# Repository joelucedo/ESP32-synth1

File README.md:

## ESP32 SYNTH
***ESP32 Wrover E/IE based synthesizer***

## STATUS
Work in progress.
</br>
## SPECS
Audio in/out and headphone,  MIDI in/out/thru, 16 pot + 1 volume pot, USB-C, reset switch

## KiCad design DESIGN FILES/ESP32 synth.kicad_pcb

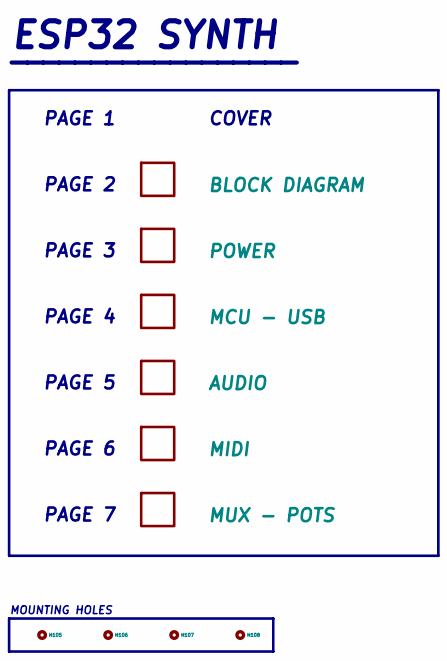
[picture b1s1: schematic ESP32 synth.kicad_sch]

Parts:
H105, H106, H107, H108: MountingHole; MountingHole_2.5mm

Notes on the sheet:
PAGE 4
COVER
PAGE 2
PAGE 5
ESP32 SYNTH
PAGE 6
MOUNTING HOLES
__________________
PAGE 7
PAGE 1
PAGE 3

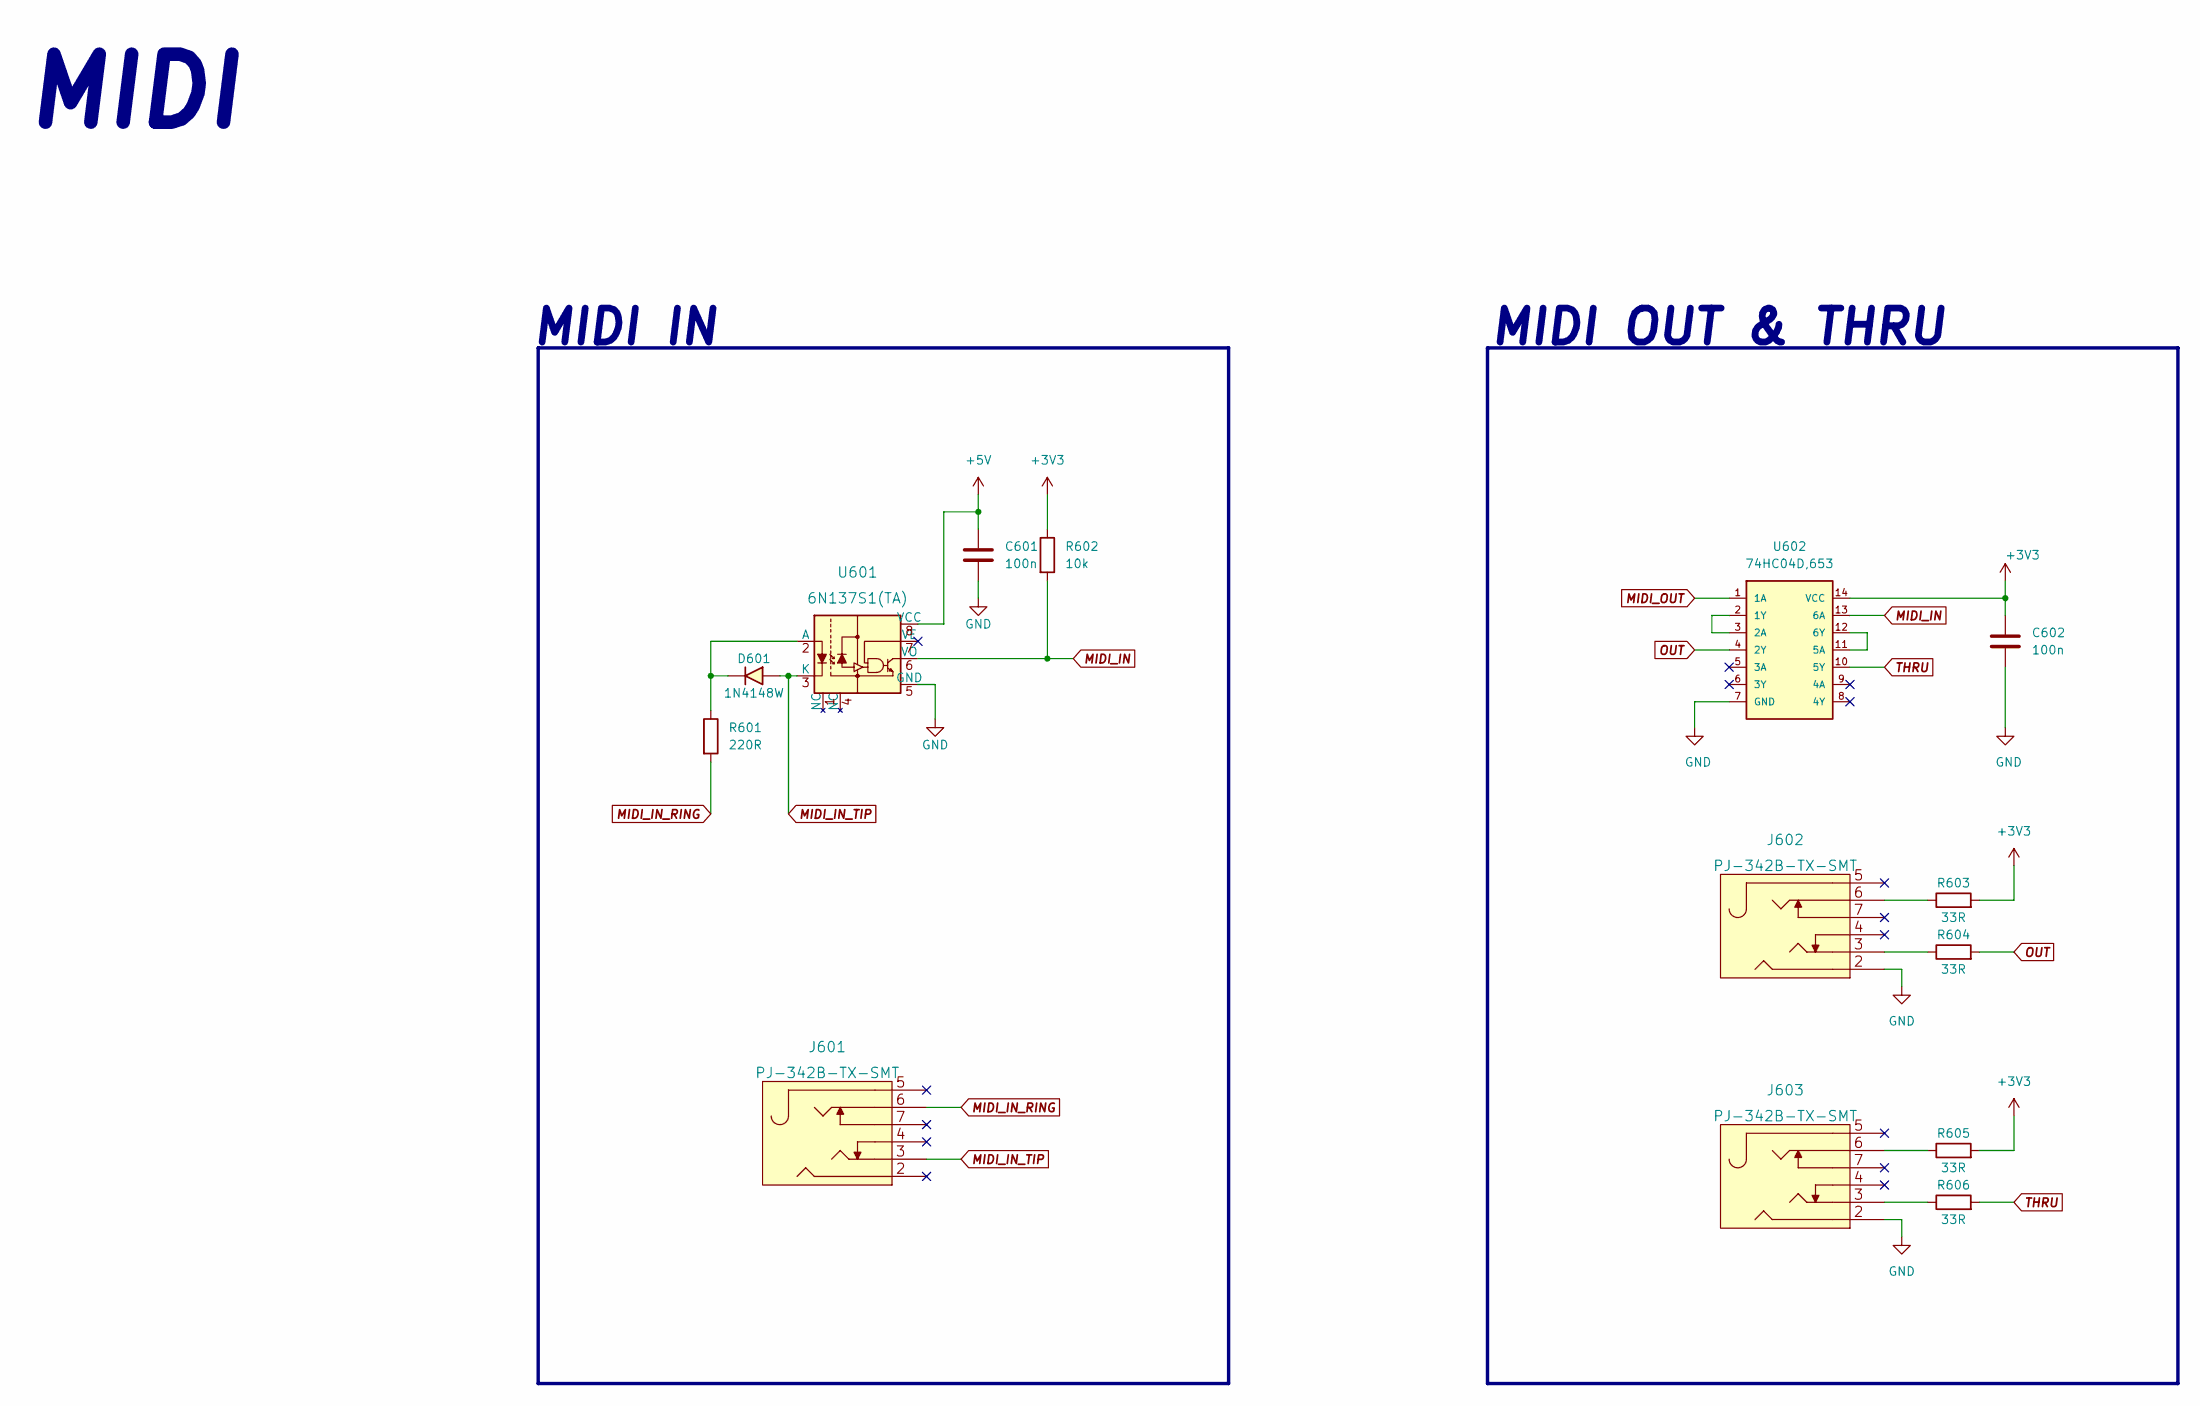
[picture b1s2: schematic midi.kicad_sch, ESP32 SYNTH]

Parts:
C601, C602: 100n; CC0603KRX7R9BB104_0603
D601: 1N4148W; 1N4148W_SOD-123
J601, J602, J603: PJ-342B-TX-SMT
R601: 220R; 0603WAF2200T5E
R602: 10k; 0603WAF1002T5E
R603, R604, R605, R606: 33R; 0603WAF330JT5E
U601: 6N137S1(TA); 6N137S1_TA_SMD-8P; MPN 6N137; Digi-Key_PN 160-1791-ND
U602: 74HC04D,653; 74HC04D_653_SOIC-14; MPN 74HC04D,653

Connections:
+3V3: C602.1, R602.1, R603.2, R605.2, U602.14 (VCC); also elsewhere on the board
+5V: C601.1, U601.8 (VCC); also elsewhere on the board
GND: C601.2, C602.2, J602.2, J603.2, U601.5 (GND), U602.7 (GND); also elsewhere on the board
MIDI_IN: R602.2, U601.6 (VO), U602.13 (6A); also elsewhere on the board
MIDI_IN_RING: J601.6, R601.2
MIDI_IN_TIP: D601.2 (A), J601.3, U601.3 (K)
MIDI_OUT: U602.1 (1A); also elsewhere on the board
unnamed: D601.1 (K), R601.1, U601.2 (A)
unnamed: J602.3, R604.1
unnamed: J602.6, R603.1
unnamed: J603.3, R606.1
unnamed: J603.6, R605.1
unnamed: U602.2 (1Y), U602.3 (2A)
unnamed: U602.11 (5A), U602.12 (6Y)
OUT: R604.2, U602.4 (2Y)
THRU: R606.2, U602.10 (5Y)

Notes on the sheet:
MIDI OUT & THRU
MIDI IN
MIDI

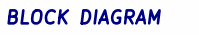
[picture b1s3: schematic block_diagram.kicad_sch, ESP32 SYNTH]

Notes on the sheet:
BLOCK DIAGRAM

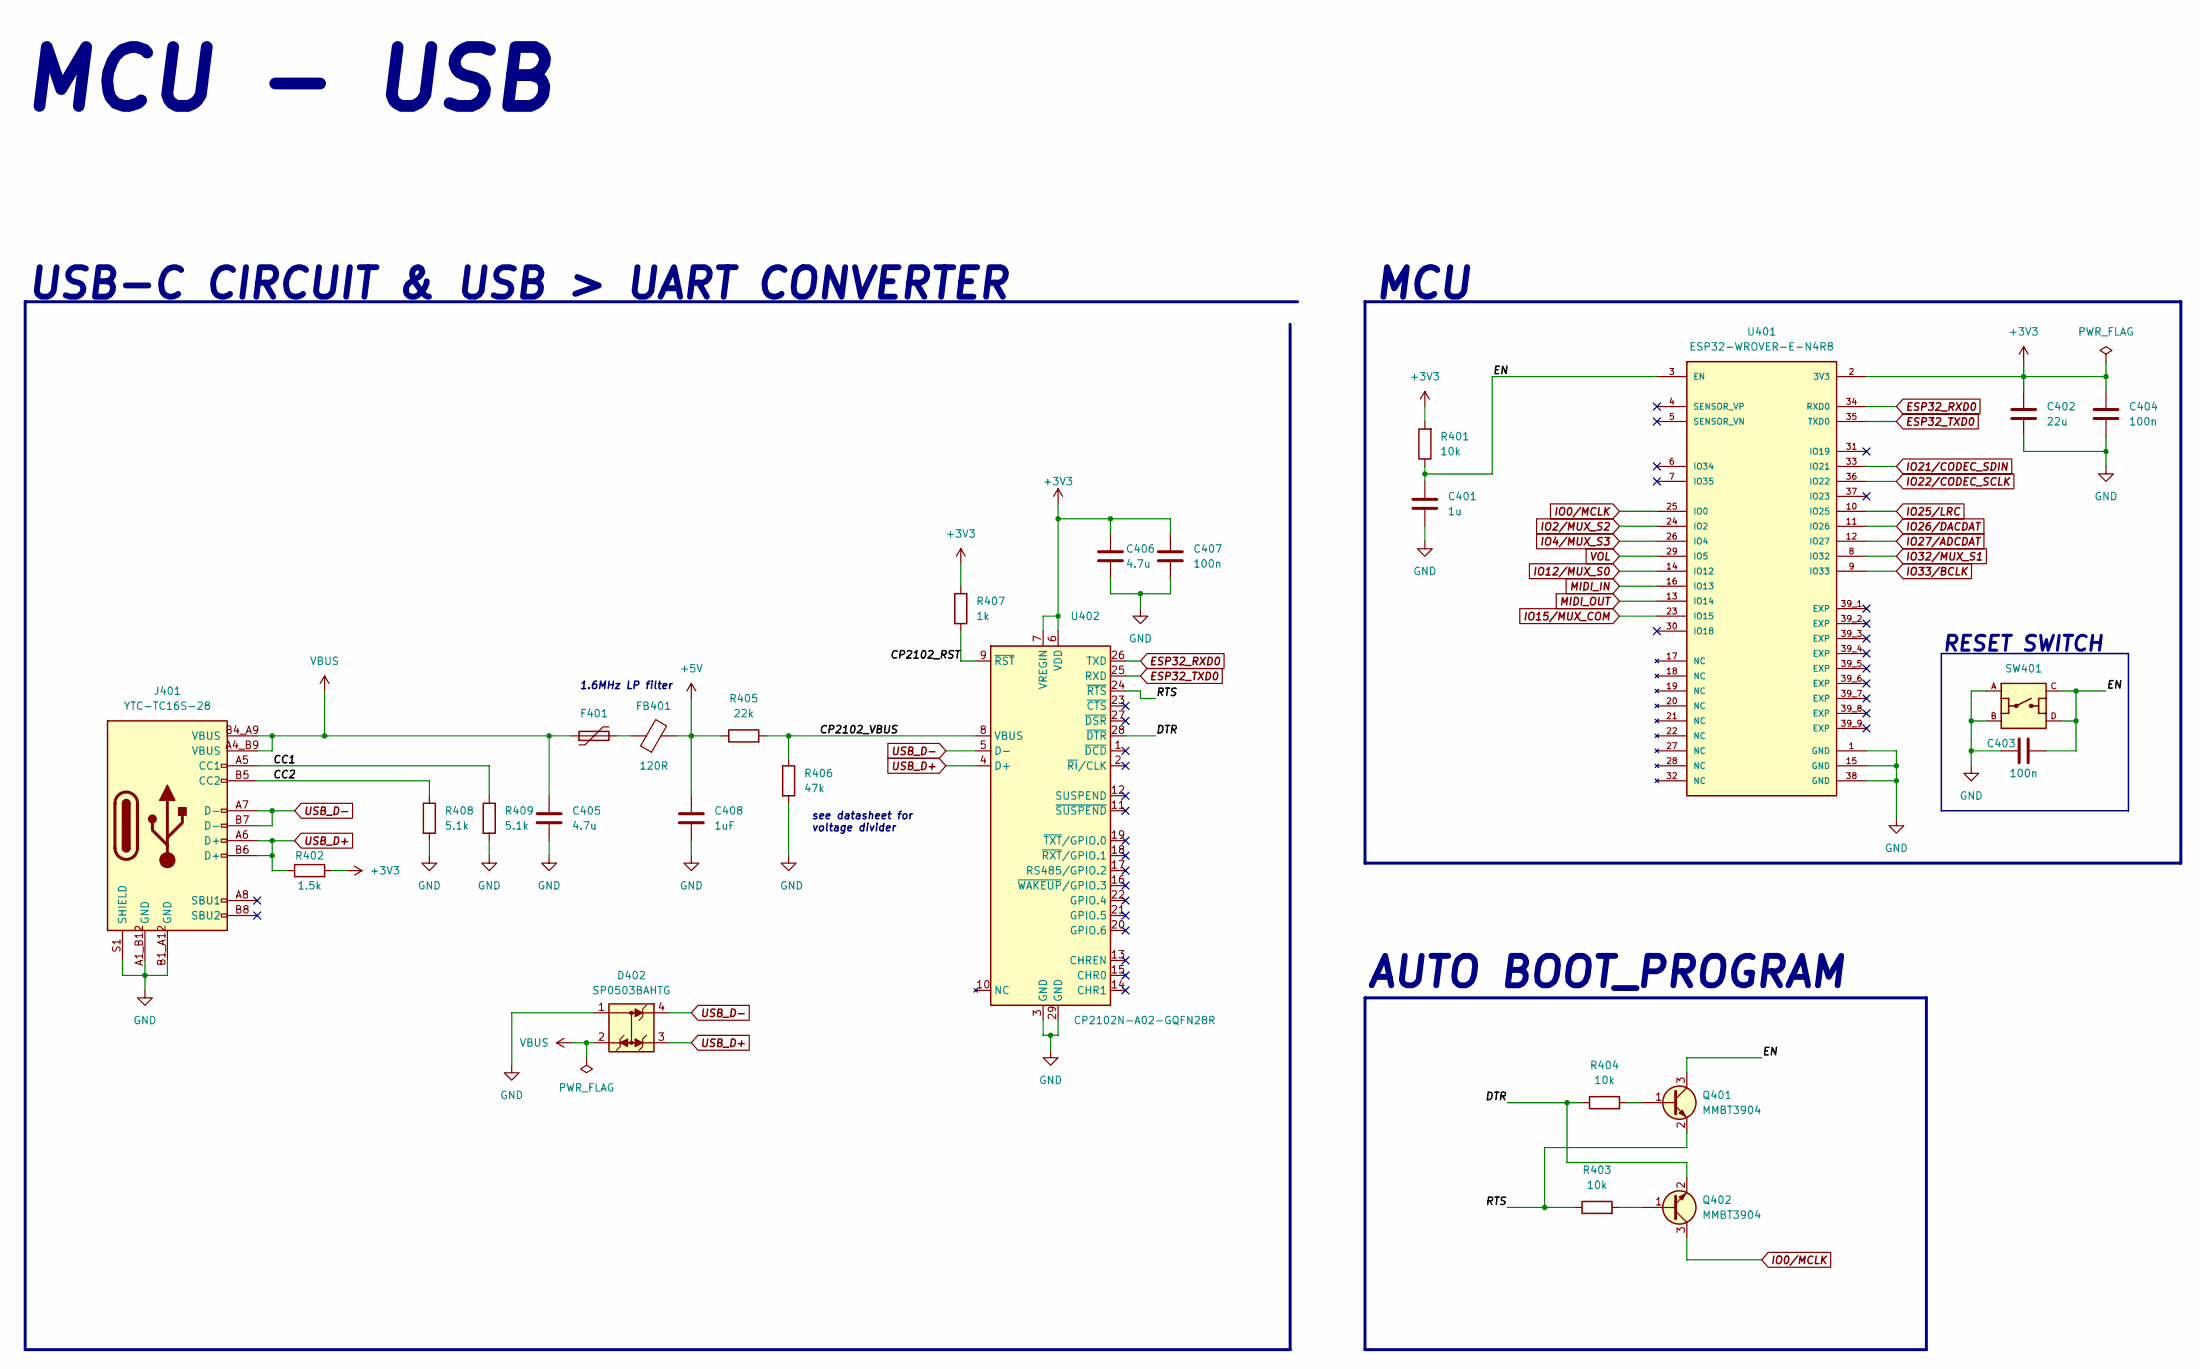
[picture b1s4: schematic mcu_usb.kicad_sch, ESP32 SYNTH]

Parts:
C401: 1u; CL10A105KB8NNNC_0603
C402: 22u; 0603_CL10A226MQ8NRNC
C403, C404, C407: 100n; CC0603KRX7R9BB104_0603
C405, C406: 4.7u; CL10A475KO8NNNC_0603
C408: 1uF; CL10A105KB8NNNC_0603
D402: SP0503BAHTG; SP0503BAHTG_SOT-143; MPN SP0503BAHTG; Digi-Key_PN F2715CT-ND
F401: SMD0805P020TF; 0805_SMD0805P020TF
FB401: 120R; 0603_BLM18AG121SN1D
J401: YTC-TC16S-28
Q401, Q402: MMBT3904; MMBT3904_SOT-23
R401, R403, R404: 10k; 0603WAF1002T5E
R402: 1.5k; CQ03WAJ0152T5E
R405: 22k; 0603WAF2202T5E
R406: 47k; 0603WAF4702T5E
R407: 1k; 0603WAF1001T5E
R408, R409: 5.1k; 0603WAF5101T5E
SW401: TS-1187A-B-A-B; TS-1187A-B-A-B_smd
U401: ESP32-WROVER-E-N4R8; XCVR_ESP32-WROVER-E-N4R8; PARTREV 1.6
U402: CP2102N-A02-GQFN28R; CP2102N-A02-GQFN28R_QFN-28

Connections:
+3V3: C402.1, C404.1, C406.1, C407.1, R401.2, R402.2, R407.1, U401.2 (3V3), U402.6 (VDD), U402.7 (VREGIN); also elsewhere on the board
+5V: C408.1, FB401.2, R405.1; also elsewhere on the board
/MCU - USB/CC1: J401.A5 (CC1), R409.1
/MCU - USB/CC2: J401.B5 (CC2), R408.1
/MCU - USB/CP2102_RST: R407.2, U402.9 (~RST)
/MCU - USB/CP2102_VBUS: R405.2, R406.1, U402.8 (VBUS)
/MCU - USB/DTR: Q402.2 (E), R404.1, U402.28 (~DTR)
/MCU - USB/EN: C401.1, C403.2, Q401.3 (C), R401.1, SW401.C, SW401.D, U401.3 (EN)
/MCU - USB/RTS: Q401.2 (E), R403.1, U402.24 (~RTS)
ESP32_RXD0: U401.34 (RXD0), U402.26 (TXD)
ESP32_TXD0: U401.35 (TXD0), U402.25 (RXD)
GND: C401.2, C402.2, C403.1, C404.2, C405.2, C406.2, C407.2, C408.2, D402.1, J401.A1_B12 (GND), J401.B1_A12 (GND), J401.S1 (SHIELD), R406.2, R408.2, R409.2, SW401.A, SW401.B, U401.1 (GND), U401.15 (GND), U401.38 (GND), U402.3 (GND), U402.29 (GND); also elsewhere on the board
IO0/MCLK: Q402.3 (C), U401.25 (IO0); also elsewhere on the board
IO2/MUX_S2: U401.24 (IO2); also elsewhere on the board
IO4/MUX_S3: U401.26 (IO4); also elsewhere on the board
IO12/MUX_S0: U401.14 (IO12); also elsewhere on the board
IO15/MUX_COM: U401.23 (IO15); also elsewhere on the board
IO21/CODEC_SDIN: U401.33 (IO21); also elsewhere on the board
IO22/CODEC_SCLK: U401.36 (IO22); also elsewhere on the board
IO25/LRC: U401.10 (IO25); also elsewhere on the board
IO26/DACDAT: U401.11 (IO26); also elsewhere on the board
IO27/ADCDAT: U401.12 (IO27); also elsewhere on the board
IO32/MUX_S1: U401.8 (IO32); also elsewhere on the board
IO33/BCLK: U401.9 (IO33); also elsewhere on the board
MIDI_IN: U401.16 (IO13); also elsewhere on the board
MIDI_OUT: U401.13 (IO14); also elsewhere on the board
unnamed: F401.2, FB401.1
unnamed: Q401.1 (B), R404.2
unnamed: Q402.1 (B), R403.2
USB_D+: D402.3, J401.A6 (D+), J401.B6 (D+), R402.1, U402.4 (D+)
USB_D-: D402.4, J401.A7 (D-), J401.B7 (D-), U402.5 (D-)
VBUS: C405.1, D402.2, F401.1, J401.A4_B9 (VBUS), J401.B4_A9 (VBUS)
VOL: U401.29 (IO5); also elsewhere on the board

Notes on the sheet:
USB-C CIRCUIT & USB > UART CONVERTER
see datasheet for voltage divider
RESET SWITCH
MCU
1.6MHz LP filter
AUTO BOOT_PROGRAM
MCU - USB

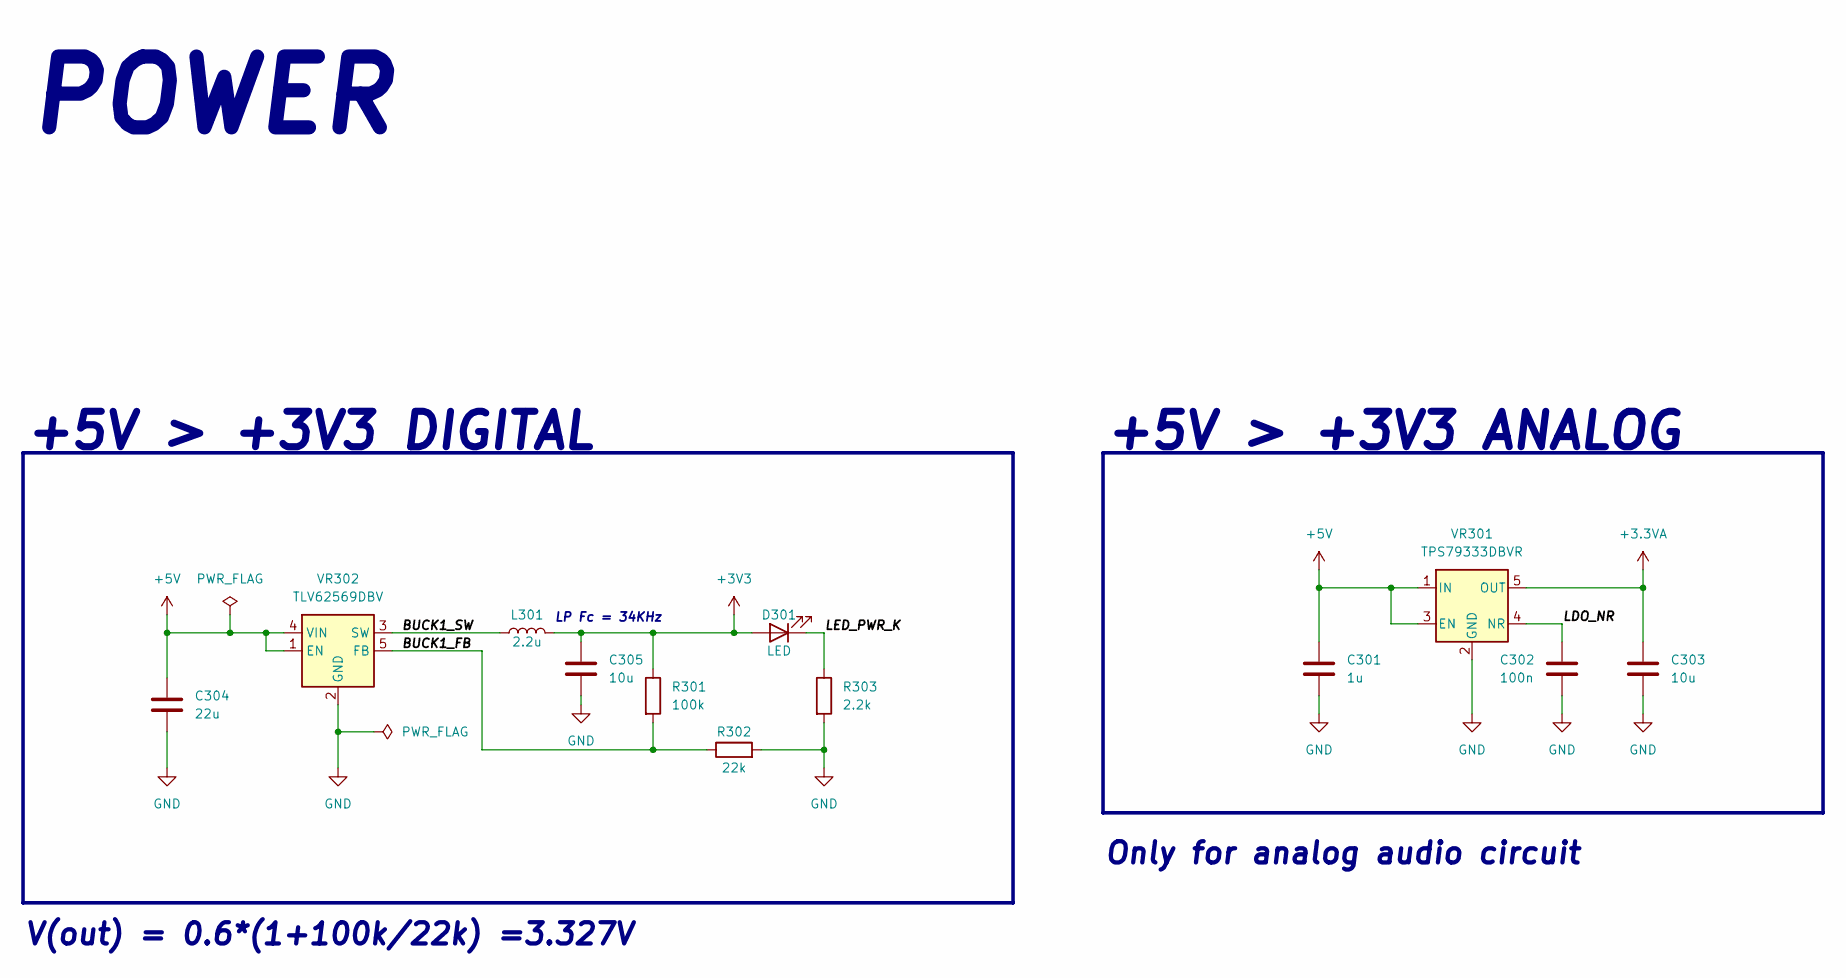
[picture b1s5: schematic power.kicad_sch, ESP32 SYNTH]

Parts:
C301: 1u; CL10A105KB8NNNC_0603
C302: 100n; CC0603KRX7R9BB104_0603
C303: 10u; 0603_CL10A106KP8NNNC
C304: 22u; 0603_CL10A226MQ8NRNC
C305: 10u; CL10A106MA8NRNC_0603
D301: LED; LED_D3.0mm
L301: 2.2u; CD32YP0302-2R2M
R301: 100k; 0603WAF1003T5E
R302: 22k; 0603WAF2200T5E
R303: 2.2k; 0603WAF2201T5E
VR301: TPS79333DBVR; TPS79333DBVR_SOT-23-5
VR302: TLV62569DBV; TLV62569DBVR

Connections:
+3.3VA: C303.1, VR301.5 (OUT); also elsewhere on the board
+3V3: C305.1, D301.2 (A), L301.2, R301.1; also elsewhere on the board
+5V: C301.1, C304.1, VR301.1 (IN), VR301.3 (EN), VR302.1 (EN), VR302.4 (VIN); also elsewhere on the board
/POWER/BUCK1_FB: R301.2, R302.1, VR302.5 (FB)
/POWER/BUCK1_SW: L301.1, VR302.3 (SW)
/POWER/LDO_NR: C302.1, VR301.4 (NR)
/POWER/LED_PWR_K: D301.1 (K), R303.1
GND: C301.2, C302.2, C303.2, C304.2, C305.2, R302.2, R303.2, VR301.2 (GND), VR302.2 (GND); also elsewhere on the board

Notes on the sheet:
POWER
LP Fc = 34KHz
+5V > +3V3 DIGITAL
+5V > +3V3 ANALOG
Only for analog audio circuit
V(out) = 0.6*(1+100k/22k) =3.327V

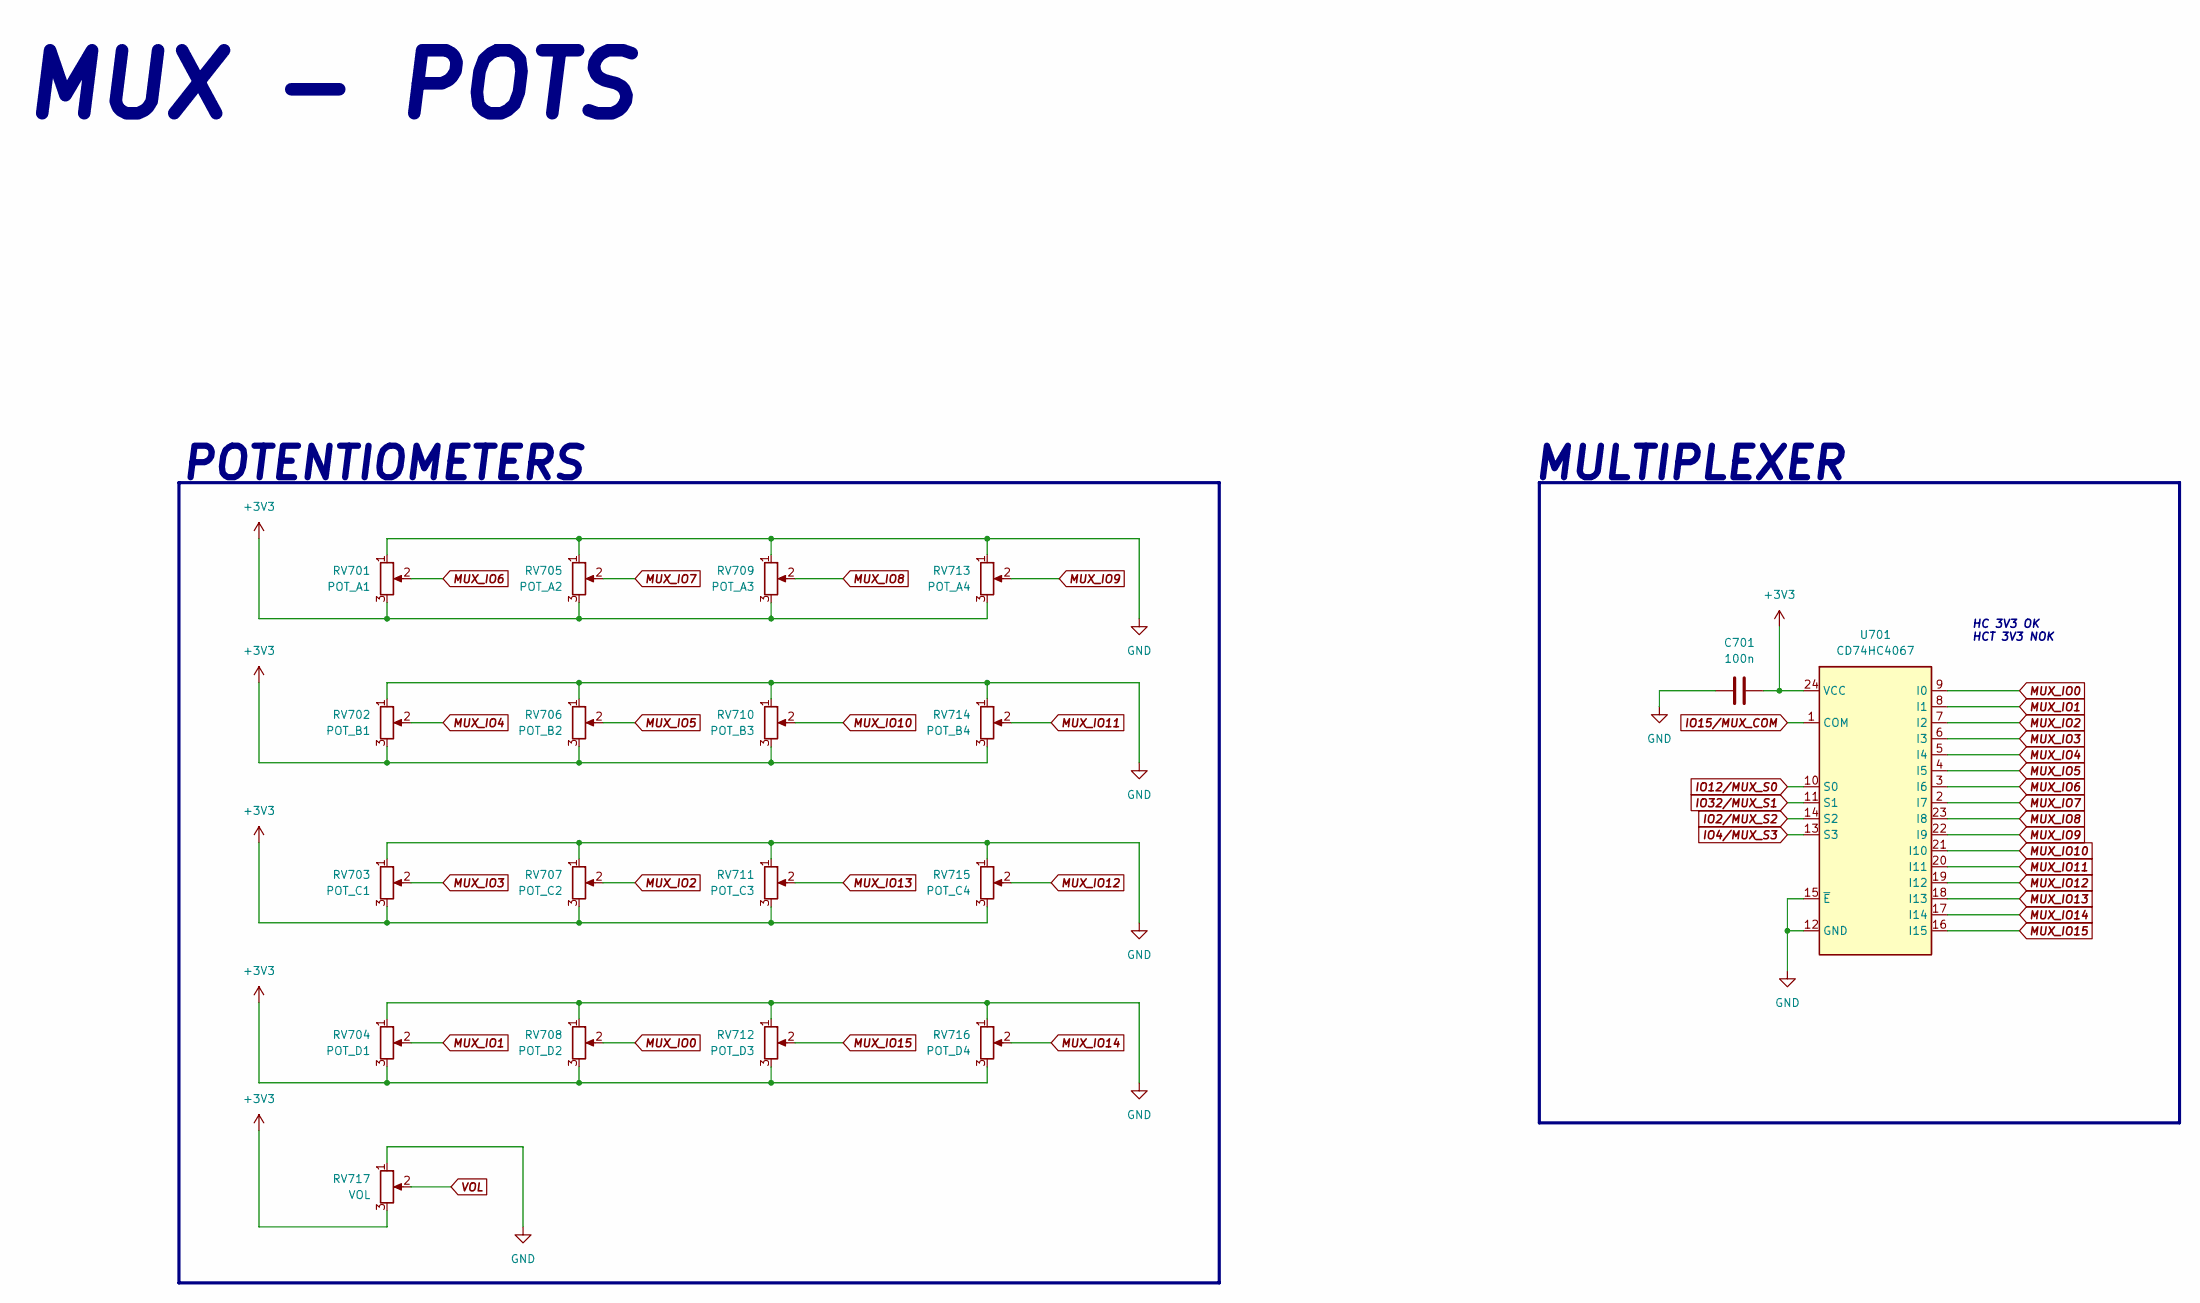
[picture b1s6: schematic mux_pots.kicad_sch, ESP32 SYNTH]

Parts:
C701: 100n; CC0603KRX7R9BB104_0603
RV701: POT_A1; RK09D1130C2P
RV702: POT_B1; RK09D1130C2P
RV703: POT_C1; RK09D1130C2P
RV704: POT_D1; RK09D1130C2P
RV705: POT_A2; RK09D1130C2P
RV706: POT_B2; RK09D1130C2P
RV707: POT_C2; RK09D1130C2P
RV708: POT_D2; RK09D1130C2P
RV709: POT_A3; RK09D1130C2P
RV710: POT_B3; RK09D1130C2P
RV711: POT_C3; RK09D1130C2P
RV712: POT_D3; RK09D1130C2P
RV713: POT_A4; RK09D1130C2P
RV714: POT_B4; RK09D1130C2P
RV715: POT_C4; RK09D1130C2P
RV716: POT_D4; RK09D1130C2P
RV717: VOL; RK09D1130C2P
U701: CD74HC4067; CD74HC4067_SOIC-24

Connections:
+3V3: C701.2, RV701.3, RV702.3, RV703.3, RV704.3, RV705.3, RV706.3, RV707.3, RV708.3, RV709.3, RV710.3, RV711.3, RV712.3, RV713.3, RV714.3, RV715.3, RV716.3, RV717.3, U701.24 (VCC); also elsewhere on the board
GND: C701.1, RV701.1, RV702.1, RV703.1, RV704.1, RV705.1, RV706.1, RV707.1, RV708.1, RV709.1, RV710.1, RV711.1, RV712.1, RV713.1, RV714.1, RV715.1, RV716.1, RV717.1, U701.12 (GND), U701.15 (~E); also elsewhere on the board
IO2/MUX_S2: U701.14 (S2); also elsewhere on the board
IO4/MUX_S3: U701.13 (S3); also elsewhere on the board
IO12/MUX_S0: U701.10 (S0); also elsewhere on the board
IO15/MUX_COM: U701.1 (COM); also elsewhere on the board
IO32/MUX_S1: U701.11 (S1); also elsewhere on the board
MUX_IO0: RV708.2, U701.9 (I0)
MUX_IO1: RV704.2, U701.8 (I1)
MUX_IO2: RV707.2, U701.7 (I2)
MUX_IO3: RV703.2, U701.6 (I3)
MUX_IO4: RV702.2, U701.5 (I4)
MUX_IO5: RV706.2, U701.4 (I5)
MUX_IO6: RV701.2, U701.3 (I6)
MUX_IO7: RV705.2, U701.2 (I7)
MUX_IO8: RV709.2, U701.23 (I8)
MUX_IO9: RV713.2, U701.22 (I9)
MUX_IO10: RV710.2, U701.21 (I10)
MUX_IO11: RV714.2, U701.20 (I11)
MUX_IO12: RV715.2, U701.19 (I12)
MUX_IO13: RV711.2, U701.18 (I13)
MUX_IO14: RV716.2, U701.17 (I14)
MUX_IO15: RV712.2, U701.16 (I15)
VOL: RV717.2; also elsewhere on the board

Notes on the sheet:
MULTIPLEXER
POTENTIOMETERS
MUX - POTS
HC 3V3 OK HCT 3V3 NOK

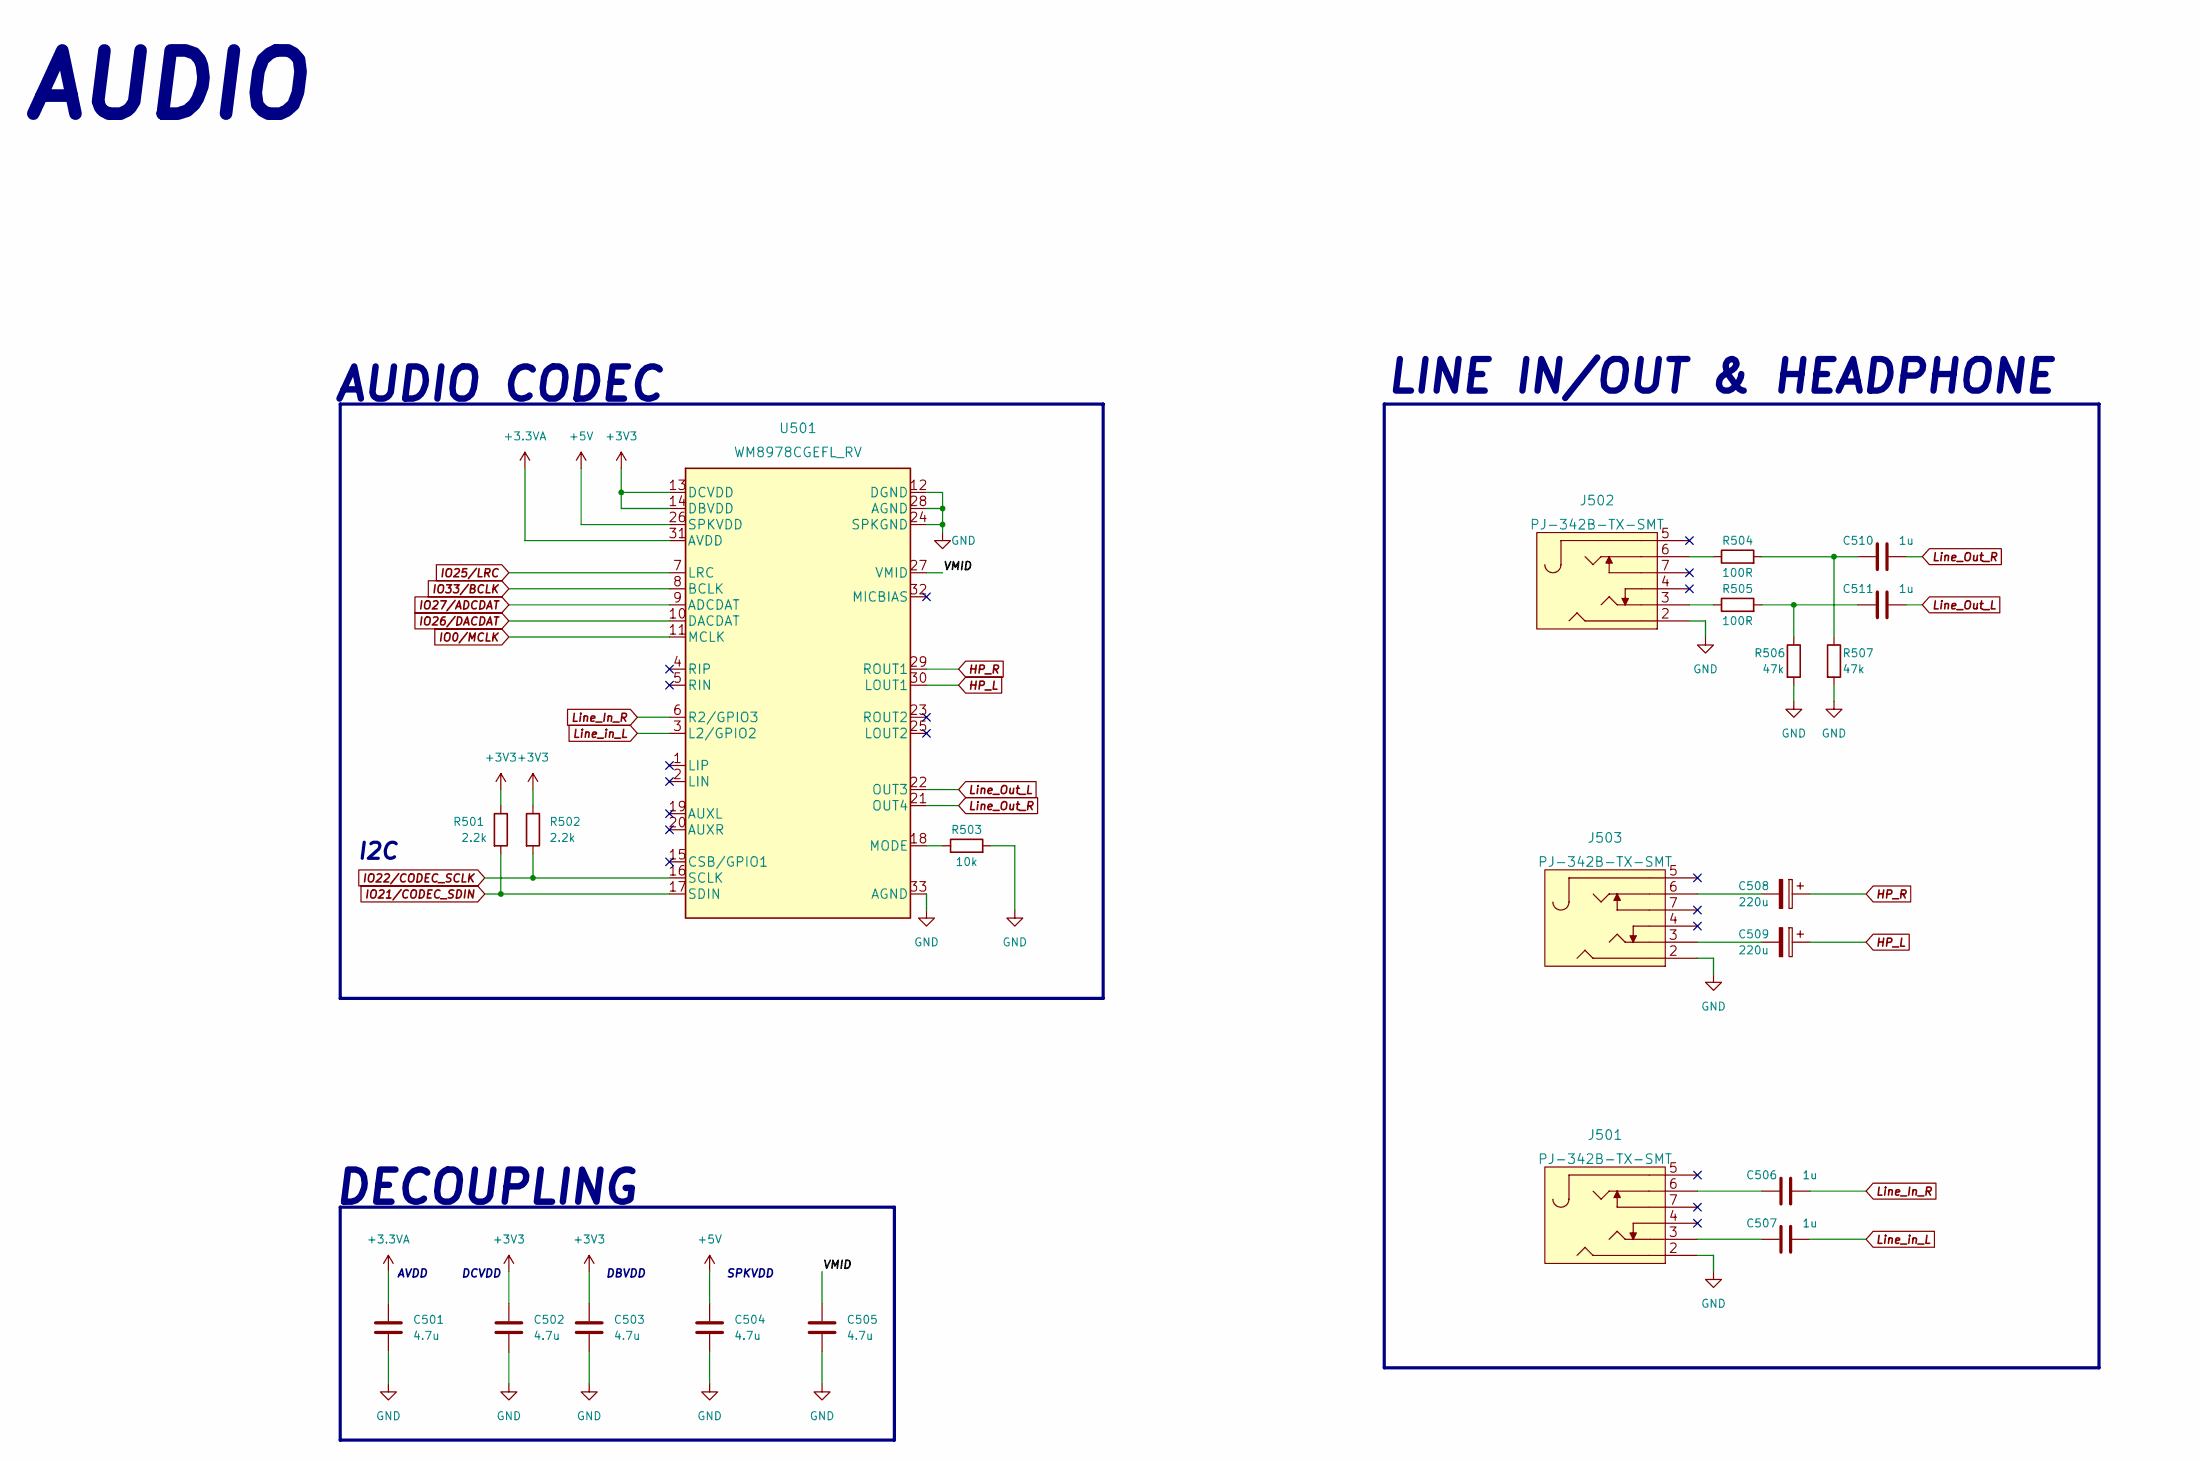
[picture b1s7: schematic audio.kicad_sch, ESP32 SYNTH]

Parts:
C501, C502, C503, C504, C505: 4.7u; CL10A475KO8NNNC_0603
C506, C507, C510, C511: 1u; CL10A105KB8NNNC_0603
C508, C509: 220u; RVT1A221M0605
J501, J502, J503: PJ-342B-TX-SMT
R501, R502: 2.2k; 0603WAF2201T5E
R503: 10k; 0603WAF1002T5E
R504, R505: 100R; 0603WAF1000T5E
R506, R507: 47k; 0603WAF4702T5E
U501: WM8978CGEFL_RV; WM8978CGEFL_RV_WQFN-32

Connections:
+3.3VA: C501.1, U501.31 (AVDD); also elsewhere on the board
+3V3: C502.1, C503.1, R501.1, R502.1, U501.13 (DCVDD), U501.14 (DBVDD); also elsewhere on the board
+5V: C504.1, U501.26 (SPKVDD); also elsewhere on the board
/AUDIO/VMID: C505.1, U501.27 (VMID)
GND: C501.2, C502.2, C503.2, C504.2, C505.2, J501.2, J502.2, J503.2, R503.2, R506.2, R507.2, U501.12 (DGND), U501.24 (SPKGND), U501.28 (AGND), U501.33 (AGND); also elsewhere on the board
HP_L: C509.1, U501.30 (LOUT1)
HP_R: C508.1, U501.29 (ROUT1)
IO0/MCLK: U501.11 (MCLK); also elsewhere on the board
IO21/CODEC_SDIN: R501.2, U501.17 (SDIN); also elsewhere on the board
IO22/CODEC_SCLK: R502.2, U501.16 (SCLK); also elsewhere on the board
IO25/LRC: U501.7 (LRC); also elsewhere on the board
IO26/DACDAT: U501.10 (DACDAT); also elsewhere on the board
IO27/ADCDAT: U501.9 (ADCDAT); also elsewhere on the board
IO33/BCLK: U501.8 (BCLK); also elsewhere on the board
Line_In_R: C506.2, U501.6 (R2/GPIO3)
Line_Out_L: C511.2, U501.22 (OUT3)
Line_Out_R: C510.2, U501.21 (OUT4)
Line_in_L: C507.2, U501.3 (L2/GPIO2)
unnamed: C506.1, J501.6
unnamed: C507.1, J501.3
unnamed: C508.2, J503.6
unnamed: C509.2, J503.3
unnamed: C510.1, R504.2, R507.1
unnamed: C511.1, R505.2, R506.1
unnamed: J502.3, R505.1
unnamed: J502.6, R504.1
unnamed: R503.1, U501.18 (MODE)

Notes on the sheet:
AUDIO CODEC
AUDIO
AVDD
DBVDD
DECOUPLING
I2C
SPKVDD
DCVDD
LINE IN/OUT & HEADPHONE

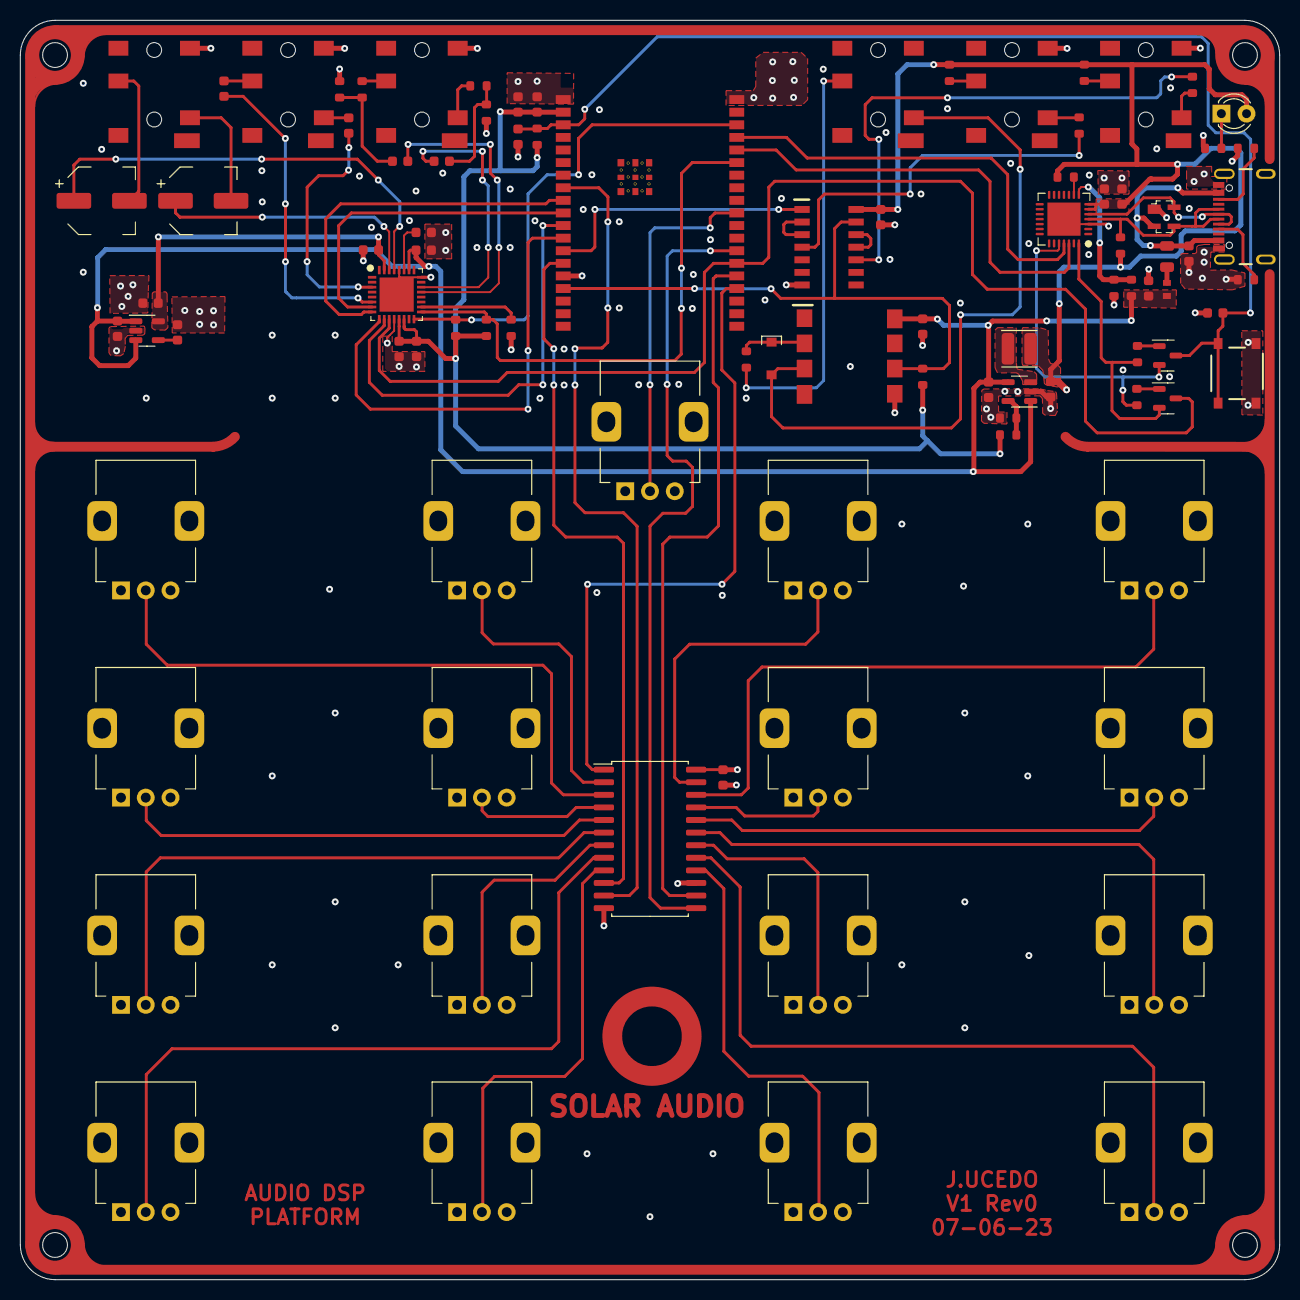
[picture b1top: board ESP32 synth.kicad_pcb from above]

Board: 4 copper layers, 127.0 x 127.0 mm, 97 parts (0 on the bottom side), 81 nets.

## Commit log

2023-06-05 new schematic pdf
2023-06-07 image add

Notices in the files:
parts and their libraries:
Copyright 2021 Accelerated Designs. All rights reserved.
